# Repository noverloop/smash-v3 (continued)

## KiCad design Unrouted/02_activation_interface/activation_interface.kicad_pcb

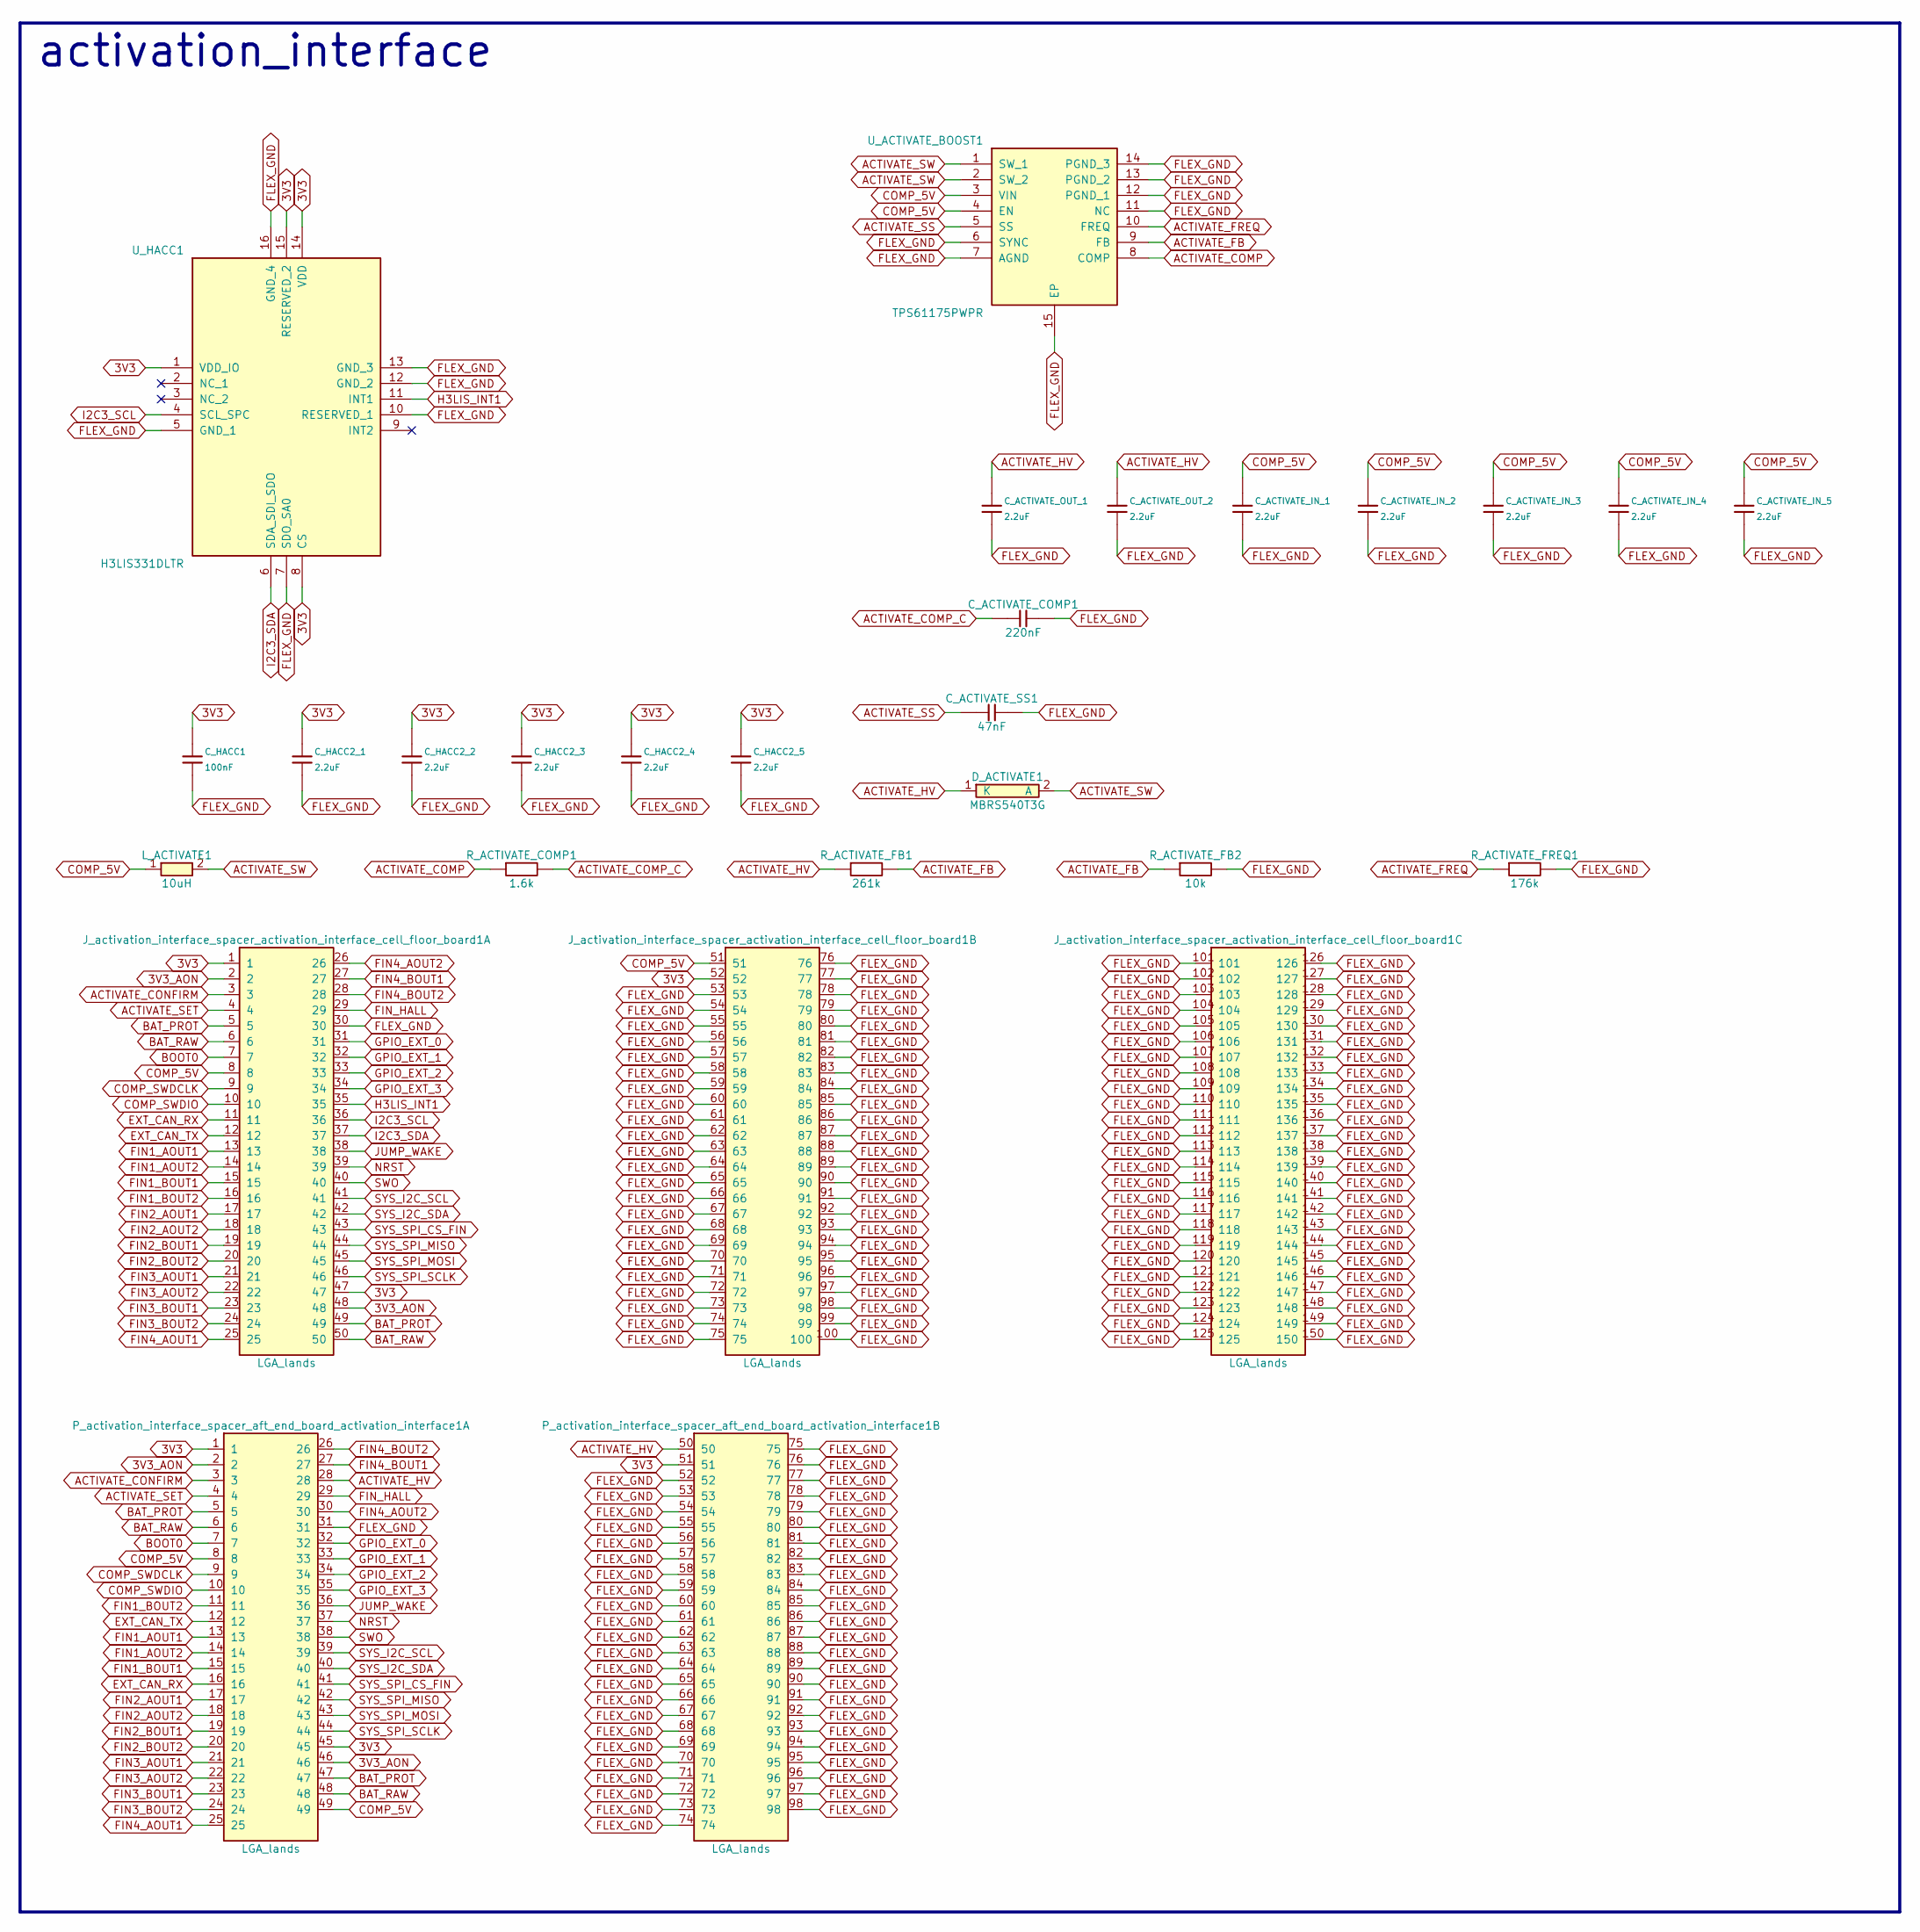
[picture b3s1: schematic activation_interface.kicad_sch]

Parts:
C_ACTIVATE_COMP1: 220nF; Capacitor_SMD_C_0603_1608Metric; MPN C-Series MIL-PRF-32535 X7R 0603 220nF
C_ACTIVATE_IN_1, C_ACTIVATE_IN_2, C_ACTIVATE_IN_3, C_ACTIVATE_IN_4, C_ACTIVATE_IN_5: 2.2uF; Capacitor_SMD_C_0603_1608Metric; MPN C-Series MIL-PRF-32535 X7R 0603 2.2uF
C_ACTIVATE_OUT_1, C_ACTIVATE_OUT_2: 2.2uF; Capacitor_SMD_C_0603_1608Metric; MPN C-Series MIL-PRF-32535 X7R 0603 2.2uF
C_ACTIVATE_SS1: 47nF; Capacitor_SMD_C_0402_1005Metric; MPN C0402 X7R 47nF
C_HACC1: 100nF; Capacitor_SMD_C_0402_1005Metric; MPN C0402 X7R 100nF
C_HACC2_1, C_HACC2_2, C_HACC2_3, C_HACC2_4, C_HACC2_5: 2.2uF; Capacitor_SMD_C_0603_1608Metric; MPN C-Series MIL-PRF-32535 X7R 0603 2.2uF
D_ACTIVATE1: MBRS540T3G; DIOM7958X256N; MPN MBRS540T3G
J_activation_interface_spacer_activation_interface_cell_floor_board1: LGA_lands; J_activation_interface_spacer_activation_interface_cell_flo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; MPN LGA_lands
L_ACTIVATE1: 10uH; INDPM4848X280N; MPN 744043100
P_activation_interface_spacer_aft_end_board_activation_interface1: LGA_lands; P_activation_interface_spacer_aft_end_board_activation_inte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; MPN LGA_lands
R_ACTIVATE_COMP1: 1.6k; Resistor_SMD_R_0402_1005Metric; MPN CRCW0402 1.6k 1% e3
R_ACTIVATE_FB1: 261k; Resistor_SMD_R_0402_1005Metric; MPN CRCW0402 261k 1% e3
R_ACTIVATE_FB2: 10k; Resistor_SMD_R_0402_1005Metric; MPN CRCW0402 10k 1% e3
R_ACTIVATE_FREQ1: 176k; Resistor_SMD_R_0402_1005Metric; MPN CRCW0402 176k 1% e3
U_ACTIVATE_BOOST1: TPS61175PWPR; SOP65P640X120-15N; MPN TPS61175PWPR
U_HACC1: H3LIS331DLTR; LIS3DHTR (LGA-16); MPN H3LIS331DLTR

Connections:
3V3: C_HACC1.1, C_HACC2_1.1, C_HACC2_2.1, C_HACC2_3.1, C_HACC2_4.1, C_HACC2_5.1, J_activation_interface_spacer_activatio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.1, J_activation_interface_spacer_activatio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.47, J_activation_interface_spacer_activatio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.52, P_activation_interface_spacer_aft_end_b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.1, P_activation_interface_spacer_aft_end_b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.45, P_activation_interface_spacer_aft_end_b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.51, U_HACC1.1 (VDD_IO), U_HACC1.8 (CS), U_HACC1.14 (VDD), U_HACC1.15 (RESERVED_2)
3V3_AON: J_activation_interface_spacer_activatio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.2, J_activation_interface_spacer_activatio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.48, P_activation_interface_spacer_aft_end_b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.2, P_activation_interface_spacer_aft_end_b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.46
ACTIVATE_COMP: R_ACTIVATE_COMP1.1, U_ACTIVATE_BOOST1.8 (COMP)
ACTIVATE_COMP_C: C_ACTIVATE_COMP1.1, R_ACTIVATE_COMP1.2
ACTIVATE_CONFIRM: J_activation_interface_spacer_activatio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.3, P_activation_interface_spacer_aft_end_b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.3
ACTIVATE_FB: R_ACTIVATE_FB1.2, R_ACTIVATE_FB2.1, U_ACTIVATE_BOOST1.9 (FB)
ACTIVATE_FREQ: R_ACTIVATE_FREQ1.1, U_ACTIVATE_BOOST1.10 (FREQ)
ACTIVATE_HV: C_ACTIVATE_OUT_1.1, C_ACTIVATE_OUT_2.1, D_ACTIVATE1.1 (K), P_activation_interface_spacer_aft_end_b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.28, P_activation_interface_spacer_aft_end_b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.50, R_ACTIVATE_FB1.1
ACTIVATE_SET: J_activation_interface_spacer_activatio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.4, P_activation_interface_spacer_aft_end_b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.4
ACTIVATE_SS: C_ACTIVATE_SS1.1, U_ACTIVATE_BOOST1.5 (SS)
ACTIVATE_SW: D_ACTIVATE1.2 (A), L_ACTIVATE1.2, U_ACTIVATE_BOOST1.1 (SW_1), U_ACTIVATE_BOOST1.2 (SW_2)
BAT_PROT: J_activation_interface_spacer_activatio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.5, J_activation_interface_spacer_activatio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.49, P_activation_interface_spacer_aft_end_b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.5, P_activation_interface_spacer_aft_end_b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.47
BAT_RAW: J_activation_interface_spacer_activatio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.6, J_activation_interface_spacer_activatio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.50, P_activation_interface_spacer_aft_end_b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.6, P_activation_interface_spacer_aft_end_b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.48
BOOT0: J_activation_interface_spacer_activatio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.7, P_activation_interface_spacer_aft_end_b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.7
COMP_5V: C_ACTIVATE_IN_1.1, C_ACTIVATE_IN_2.1, C_ACTIVATE_IN_3.1, C_ACTIVATE_IN_4.1, C_ACTIVATE_IN_5.1, J_activation_interface_spacer_activatio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.8, J_activation_interface_spacer_activatio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.51, L_ACTIVATE1.1, P_activation_interface_spacer_aft_end_b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.8, P_activation_interface_spacer_aft_end_b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.49, U_ACTIVATE_BOOST1.3 (VIN), U_ACTIVATE_BOOST1.4 (EN)
COMP_SWDCLK: J_activation_interface_spacer_activatio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.9, P_activation_interface_spacer_aft_end_b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.9
COMP_SWDIO: J_activation_interface_spacer_activatio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.10, P_activation_interface_spacer_aft_end_b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.10
EXT_CAN_RX: J_activation_interface_spacer_activatio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.11, P_activation_interface_spacer_aft_end_b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.16
EXT_CAN_TX: J_activation_interface_spacer_activatio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.12, P_activation_interface_spacer_aft_end_b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.12
FIN1_AOUT1: J_activation_interface_spacer_activatio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.13, P_activation_interface_spacer_aft_end_b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.13
FIN1_AOUT2: J_activation_interface_spacer_activatio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.14, P_activation_interface_spacer_aft_end_b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.14
FIN1_BOUT1: J_activation_interface_spacer_activatio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.15, P_activation_interface_spacer_aft_end_b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.15
FIN1_BOUT2: J_activation_interface_spacer_activatio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.16, P_activation_interface_spacer_aft_end_b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.11
FIN2_AOUT1: J_activation_interface_spacer_activatio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.17, P_activation_interface_spacer_aft_end_b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.17
FIN2_AOUT2: J_activation_interface_spacer_activatio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.18, P_activation_interface_spacer_aft_end_b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.18
FIN2_BOUT1: J_activation_interface_spacer_activatio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.19, P_activation_interface_spacer_aft_end_b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.19
FIN2_BOUT2: J_activation_interface_spacer_activatio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.20, P_activation_interface_spacer_aft_end_b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.20
FIN3_AOUT1: J_activation_interface_spacer_activatio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.21, P_activation_interface_spacer_aft_end_b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.21
FIN3_AOUT2: J_activation_interface_spacer_activatio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.22, P_activation_interface_spacer_aft_end_b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.22
FIN3_BOUT1: J_activation_interface_spacer_activatio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.23, P_activation_interface_spacer_aft_end_b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.23
FIN3_BOUT2: J_activation_interface_spacer_activatio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.24, P_activation_interface_spacer_aft_end_b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.24
FIN4_AOUT1: J_activation_interface_spacer_activatio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.25, P_activation_interface_spacer_aft_end_b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.25
FIN4_AOUT2: J_activation_interface_spacer_activatio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.26, P_activation_interface_spacer_aft_end_b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.30
FIN4_BOUT1: J_activation_interface_spacer_activatio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.27, P_activation_interface_spacer_aft_end_b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.27
FIN4_BOUT2: J_activation_interface_spacer_activatio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.28, P_activation_interface_spacer_aft_end_b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.26
FIN_HALL: J_activation_interface_spacer_activatio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.29, P_activation_interface_spacer_aft_end_b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.29
FLEX_GND: C_ACTIVATE_COMP1.2, C_ACTIVATE_IN_1.2, C_ACTIVATE_IN_2.2, C_ACTIVATE_IN_3.2, C_ACTIVATE_IN_4.2, C_ACTIVATE_IN_5.2, C_ACTIVATE_OUT_1.2, C_ACTIVATE_OUT_2.2, C_ACTIVATE_SS1.2, C_HACC1.2, C_HACC2_1.2, C_HACC2_2.2, C_HACC2_3.2, C_HACC2_4.2, C_HACC2_5.2, J_activation_interface_spacer_activatio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.30, J_activation_interface_spacer_activatio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.53, J_activation_interface_spacer_activatio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.54, J_activation_interface_spacer_activatio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.55, J_activation_interface_spacer_activatio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.56, J_activation_interface_spacer_activatio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.57, J_activation_interface_spacer_activatio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.58, J_activation_interface_spacer_activatio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.59, J_activation_interface_spacer_activatio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.60, J_activation_interface_spacer_activatio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.61, J_activation_interface_spacer_activatio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.62, J_activation_interface_spacer_activatio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.63, J_activation_interface_spacer_activatio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.64, J_activation_interface_spacer_activatio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.65, J_activation_interface_spacer_activatio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.66, J_activation_interface_spacer_activatio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.67, J_activation_interface_spacer_activatio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.68, J_activation_interface_spacer_activatio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.69, J_activation_interface_spacer_activatio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.70, J_activation_interface_spacer_activatio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.71, J_activation_interface_spacer_activatio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.72, J_activation_interface_spacer_activatio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.73, J_activation_interface_spacer_activatio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.74, J_activation_interface_spacer_activatio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.75, J_activation_interface_spacer_activatio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.76, J_activation_interface_spacer_activatio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.77, J_activation_interface_spacer_activatio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.78, J_activation_interface_spacer_activatio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.79, J_activation_interface_spacer_activatio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.80, J_activation_interface_spacer_activatio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.81, J_activation_interface_spacer_activatio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.82, J_activation_interface_spacer_activatio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.83, J_activation_interface_spacer_activatio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.84, J_activation_interface_spacer_activatio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.85, J_activation_interface_spacer_activatio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.86, J_activation_interface_spacer_activatio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.87, J_activation_interface_spacer_activatio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.88, J_activation_interface_spacer_activatio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.89, J_activation_interface_spacer_activatio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.90, J_activation_interface_spacer_activatio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.91, J_activation_interface_spacer_activatio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.92, J_activation_interface_spacer_activatio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.93, J_activation_interface_spacer_activatio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.94, J_activation_interface_spacer_activatio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.95, J_activation_interface_spacer_activatio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.96, J_activation_interface_spacer_activatio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.97, J_activation_interface_spacer_activatio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.98, J_activation_interface_spacer_activatio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.99, J_activation_interface_spacer_activatio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.100, J_activation_interface_spacer_activatio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.101, J_activation_interface_spacer_activatio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.102, J_activation_interface_spacer_activatio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.103, J_activation_interface_spacer_activatio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.104, J_activation_interface_spacer_activatio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.105, J_activation_interface_spacer_activatio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.106, J_activation_interface_spacer_activatio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.107, J_activation_interface_spacer_activatio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.108, J_activation_interface_spacer_activatio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.109, J_activation_interface_spacer_activatio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.110, J_activation_interface_spacer_activatio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.111, J_activation_interface_spacer_activatio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.112, J_activation_interface_spacer_activatio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.113, J_activation_interface_spacer_activatio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.114, J_activation_interface_spacer_activatio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.115, J_activation_interface_spacer_activatio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.116, J_activation_interface_spacer_activatio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.117, J_activation_interface_spacer_activatio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.118, J_activation_interface_spacer_activatio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.119, J_activation_interface_spacer_activatio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.120, J_activation_interface_spacer_activatio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.121, J_activation_interface_spacer_activatio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.122, J_activation_interface_spacer_activatio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.123, J_activation_interface_spacer_activatio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.124, J_activation_interface_spacer_activatio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.125, J_activation_interface_spacer_activatio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.126, J_activation_interface_spacer_activatio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.127, J_activation_interface_spacer_activatio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.128, J_activation_interface_spacer_activatio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.129, J_activation_interface_spacer_activatio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.130, J_activation_interface_spacer_activatio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.131, J_activation_interface_spacer_activatio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.132, J_activation_interface_spacer_activatio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.133, J_activation_interface_spacer_activatio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.134, J_activation_interface_spacer_activatio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.135, J_activation_interface_spacer_activatio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.136, J_activation_interface_spacer_activatio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.137, J_activation_interface_spacer_activatio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.138, J_activation_interface_spacer_activatio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.139, J_activation_interface_spacer_activatio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.140, J_activation_interface_spacer_activatio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.141, J_activation_interface_spacer_activatio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.142, J_activation_interface_spacer_activatio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.143, J_activation_interface_spacer_activatio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.144, J_activation_interface_spacer_activatio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.145, J_activation_interface_spacer_activatio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.146, J_activation_interface_spacer_activatio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.147, J_activation_interface_spacer_activatio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.148, J_activation_interface_spacer_activatio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.149, J_activation_interface_spacer_activatio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.150, P_activation_interface_spacer_aft_end_b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.31, P_activation_interface_spacer_aft_end_b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.52, P_activation_interface_spacer_aft_end_b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.53, P_activation_interface_spacer_aft_end_b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.54, P_activation_interface_spacer_aft_end_b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.55, P_activation_interface_spacer_aft_end_b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.56, P_activation_interface_spacer_aft_end_b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.57, P_activation_interface_spacer_aft_end_b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.58, P_activation_interface_spacer_aft_end_b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.59, P_activation_interface_spacer_aft_end_b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.60, P_activation_interface_spacer_aft_end_b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.61, P_activation_interface_spacer_aft_end_b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.62, P_activation_interface_spacer_aft_end_b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.63, P_activation_interface_spacer_aft_end_b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.64, P_activation_interface_spacer_aft_end_b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.65, P_activation_interface_spacer_aft_end_b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.66, P_activation_interface_spacer_aft_end_b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.67, P_activation_interface_spacer_aft_end_b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.68, P_activation_interface_spacer_aft_end_b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.69, P_activation_interface_spacer_aft_end_b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.70, P_activation_interface_spacer_aft_end_b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.71, P_activation_interface_spacer_aft_end_b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.72, P_activation_interface_spacer_aft_end_b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.73, P_activation_interface_spacer_aft_end_b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.74, P_activation_interface_spacer_aft_end_b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.75, P_activation_interface_spacer_aft_end_b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.76, P_activation_interface_spacer_aft_end_b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.77, P_activation_interface_spacer_aft_end_b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.78, P_activation_interface_spacer_aft_end_b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.79, P_activation_interface_spacer_aft_end_b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.80, P_activation_interface_spacer_aft_end_b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.81, P_activation_interface_spacer_aft_end_b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.82, P_activation_interface_spacer_aft_end_b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.83, P_activation_interface_spacer_aft_end_b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.84, P_activation_interface_spacer_aft_end_b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.85, P_activation_interface_spacer_aft_end_b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.86, P_activation_interface_spacer_aft_end_b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.87, P_activation_interface_spacer_aft_end_b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.88, P_activation_interface_spacer_aft_end_b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.89, P_activation_interface_spacer_aft_end_b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.90, P_activation_interface_spacer_aft_end_b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.91, P_activation_interface_spacer_aft_end_b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.92, P_activation_interface_spacer_aft_end_b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.93, P_activation_interface_spacer_aft_end_b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.94, P_activation_interface_spacer_aft_end_b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.95, P_activation_interface_spacer_aft_end_b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.96, P_activation_interface_spacer_aft_end_b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.97, P_activation_interface_spacer_aft_end_b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.98, R_ACTIVATE_FB2.2, R_ACTIVATE_FREQ1.2, U_ACTIVATE_BOOST1.6 (SYNC), U_ACTIVATE_BOOST1.7 (AGND), U_ACTIVATE_BOOST1.11 (NC), U_ACTIVATE_BOOST1.12 (PGND_1), U_ACTIVATE_BOOST1.13 (PGND_2), U_ACTIVATE_BOOST1.14 (PGND_3), U_ACTIVATE_BOOST1.15 (EP), U_HACC1.5 (GND_1), U_HACC1.7 (SDO_SA0), U_HACC1.10 (RESERVED_1), U_HACC1.12 (GND_2), U_HACC1.13 (GND_3), U_HACC1.16 (GND_4)
GPIO_EXT_0: J_activation_interface_spacer_activatio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.31, P_activation_interface_spacer_aft_end_b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.32
GPIO_EXT_1: J_activation_interface_spacer_activatio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.32, P_activation_interface_spacer_aft_end_b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.33
GPIO_EXT_2: J_activation_interface_spacer_activatio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.33, P_activation_interface_spacer_aft_end_b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.34
GPIO_EXT_3: J_activation_interface_spacer_activatio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.34, P_activation_interface_spacer_aft_end_b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.35
H3LIS_INT1: J_activation_interface_spacer_activatio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.35, U_HACC1.11 (INT1)
I2C3_SCL: J_activation_interface_spacer_activatio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.36, U_HACC1.4 (SCL_SPC)
I2C3_SDA: J_activation_interface_spacer_activatio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.37, U_HACC1.6 (SDA_SDI_SDO)
JUMP_WAKE: J_activation_interface_spacer_activatio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.38, P_activation_interface_spacer_aft_end_b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.36
NRST: J_activation_interface_spacer_activatio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.39, P_activation_interface_spacer_aft_end_b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.37
SWO: J_activation_interface_spacer_activatio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.40, P_activation_interface_spacer_aft_end_b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.38
SYS_I2C_SCL: J_activation_interface_spacer_activatio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.41, P_activation_interface_spacer_aft_end_b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.39
SYS_I2C_SDA: J_activation_interface_spacer_activatio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.42, P_activation_interface_spacer_aft_end_b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.40
SYS_SPI_CS_FIN: J_activation_interface_spacer_activatio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.43, P_activation_interface_spacer_aft_end_b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.41
SYS_SPI_MISO: J_activation_interface_spacer_activatio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.44, P_activation_interface_spacer_aft_end_b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.42
SYS_SPI_MOSI: J_activation_interface_spacer_activatio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.45, P_activation_interface_spacer_aft_end_b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.43
SYS_SPI_SCLK: J_activation_interface_spacer_activatio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.46, P_activation_interface_spacer_aft_end_b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.44

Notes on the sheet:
activation_interface

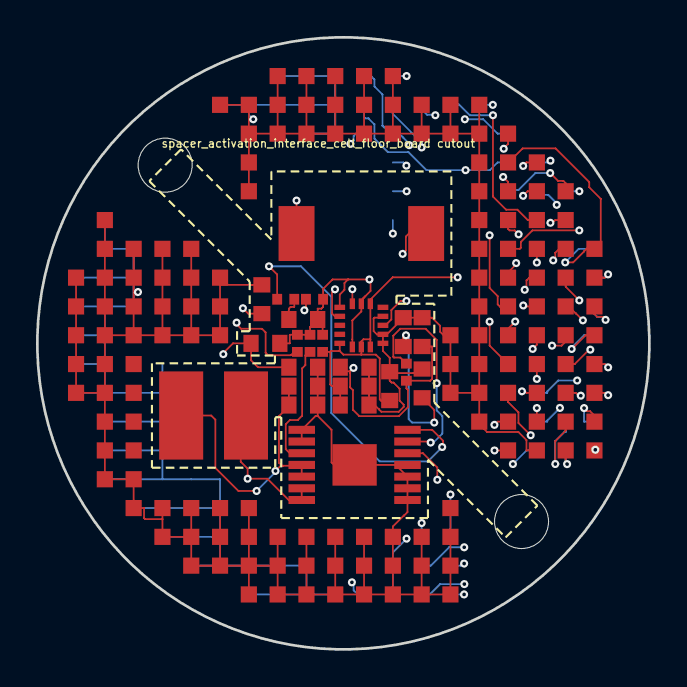
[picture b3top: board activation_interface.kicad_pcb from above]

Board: 14 copper layers, 34.0 x 34.0 mm, 27 parts (1 on the bottom side), 53 nets.

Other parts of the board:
MH1, MH2: smash_mech_potting

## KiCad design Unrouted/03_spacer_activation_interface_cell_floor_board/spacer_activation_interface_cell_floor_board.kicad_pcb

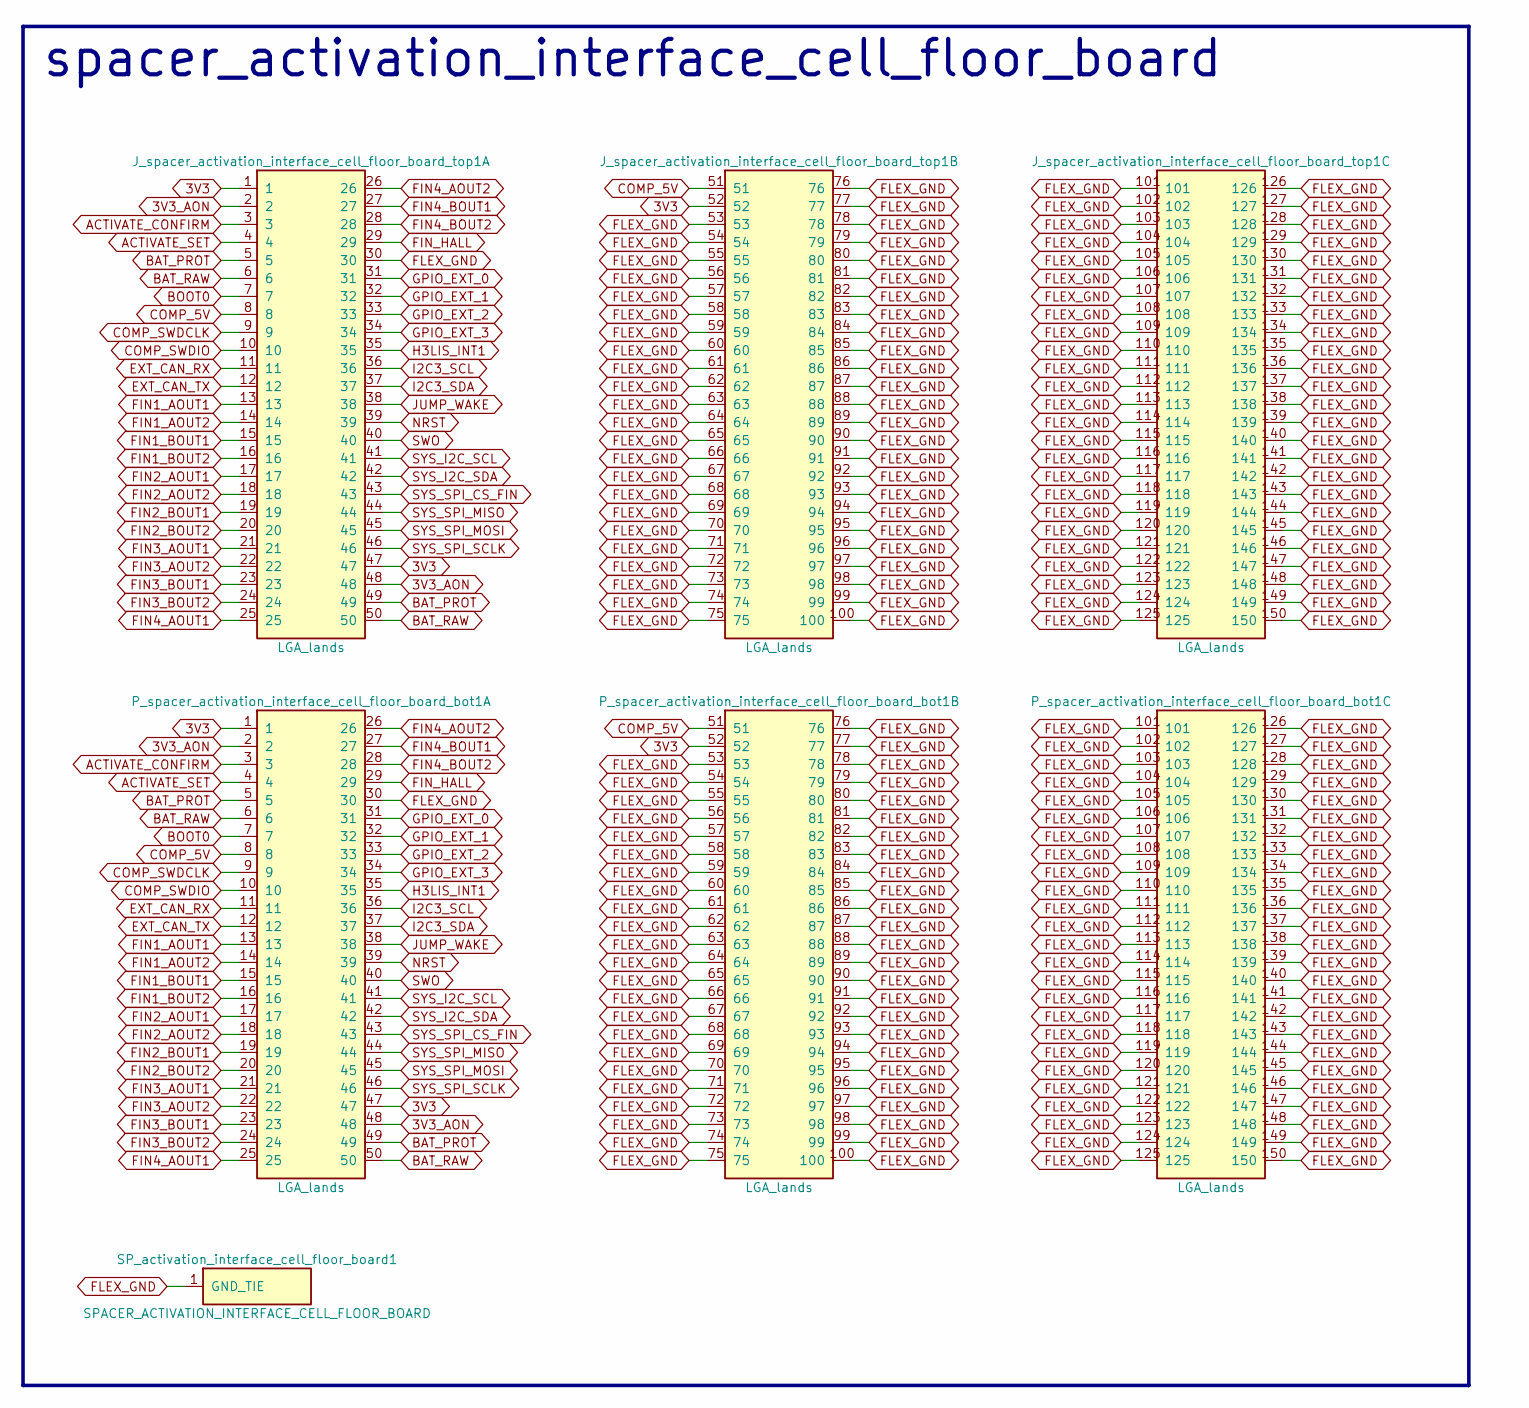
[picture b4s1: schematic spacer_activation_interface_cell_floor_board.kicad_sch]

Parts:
J_spacer_activation_interface_cell_floor_board_top1: LGA_lands; J_spacer_activation_interface_cell_floor_board_top; MPN LGA_lands
P_spacer_activation_interface_cell_floor_board_bot1: LGA_lands; P_spacer_activation_interface_cell_floor_board_bot; MPN LGA_lands
SP_activation_interface_cell_floor_board1: SPACER_ACTIVATION_INTERFACE_CELL_FLOOR_BOARD; Spacer_Mechanical_34mm

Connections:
3V3: J_spacer_activation_interface_cell_floo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.1, J_spacer_activation_interface_cell_floo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.47, J_spacer_activation_interface_cell_floo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.52, P_spacer_activation_interface_cell_floo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.1, P_spacer_activation_interface_cell_floo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.47, P_spacer_activation_interface_cell_floo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.52
3V3_AON: J_spacer_activation_interface_cell_floo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.2, J_spacer_activation_interface_cell_floo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.48, P_spacer_activation_interface_cell_floo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.2, P_spacer_activation_interface_cell_floo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.48
ACTIVATE_CONFIRM: J_spacer_activation_interface_cell_floo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.3, P_spacer_activation_interface_cell_floo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.3
ACTIVATE_SET: J_spacer_activation_interface_cell_floo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.4, P_spacer_activation_interface_cell_floo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.4
BAT_PROT: J_spacer_activation_interface_cell_floo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.5, J_spacer_activation_interface_cell_floo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.49, P_spacer_activation_interface_cell_floo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.5, P_spacer_activation_interface_cell_floo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.49
BAT_RAW: J_spacer_activation_interface_cell_floo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.6, J_spacer_activation_interface_cell_floo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.50, P_spacer_activation_interface_cell_floo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.6, P_spacer_activation_interface_cell_floo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.50
BOOT0: J_spacer_activation_interface_cell_floo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.7, P_spacer_activation_interface_cell_floo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.7
COMP_5V: J_spacer_activation_interface_cell_floo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.8, J_spacer_activation_interface_cell_floo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.51, P_spacer_activation_interface_cell_floo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.8, P_spacer_activation_interface_cell_floo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.51
COMP_SWDCLK: J_spacer_activation_interface_cell_floo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.9, P_spacer_activation_interface_cell_floo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.9
COMP_SWDIO: J_spacer_activation_interface_cell_floo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.10, P_spacer_activation_interface_cell_floo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.10
EXT_CAN_RX: J_spacer_activation_interface_cell_floo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.11, P_spacer_activation_interface_cell_floo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.11
EXT_CAN_TX: J_spacer_activation_interface_cell_floo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.12, P_spacer_activation_interface_cell_floo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.12
FIN1_AOUT1: J_spacer_activation_interface_cell_floo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.13, P_spacer_activation_interface_cell_floo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.13
FIN1_AOUT2: J_spacer_activation_interface_cell_floo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.14, P_spacer_activation_interface_cell_floo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.14
FIN1_BOUT1: J_spacer_activation_interface_cell_floo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.15, P_spacer_activation_interface_cell_floo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.15
FIN1_BOUT2: J_spacer_activation_interface_cell_floo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.16, P_spacer_activation_interface_cell_floo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.16
FIN2_AOUT1: J_spacer_activation_interface_cell_floo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.17, P_spacer_activation_interface_cell_floo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.17
FIN2_AOUT2: J_spacer_activation_interface_cell_floo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.18, P_spacer_activation_interface_cell_floo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.18
FIN2_BOUT1: J_spacer_activation_interface_cell_floo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.19, P_spacer_activation_interface_cell_floo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.19
FIN2_BOUT2: J_spacer_activation_interface_cell_floo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.20, P_spacer_activation_interface_cell_floo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.20
FIN3_AOUT1: J_spacer_activation_interface_cell_floo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.21, P_spacer_activation_interface_cell_floo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.21
FIN3_AOUT2: J_spacer_activation_interface_cell_floo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.22, P_spacer_activation_interface_cell_floo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.22
FIN3_BOUT1: J_spacer_activation_interface_cell_floo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.23, P_spacer_activation_interface_cell_floo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.23
FIN3_BOUT2: J_spacer_activation_interface_cell_floo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.24, P_spacer_activation_interface_cell_floo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.24
FIN4_AOUT1: J_spacer_activation_interface_cell_floo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.25, P_spacer_activation_interface_cell_floo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.25
FIN4_AOUT2: J_spacer_activation_interface_cell_floo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.26, P_spacer_activation_interface_cell_floo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.26
FIN4_BOUT1: J_spacer_activation_interface_cell_floo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.27, P_spacer_activation_interface_cell_floo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.27
FIN4_BOUT2: J_spacer_activation_interface_cell_floo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.28, P_spacer_activation_interface_cell_floo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.28
FIN_HALL: J_spacer_activation_interface_cell_floo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.29, P_spacer_activation_interface_cell_floo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.29
FLEX_GND: J_spacer_activation_interface_cell_floo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.30, J_spacer_activation_interface_cell_floo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.53, J_spacer_activation_interface_cell_floo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.54, J_spacer_activation_interface_cell_floo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.55, J_spacer_activation_interface_cell_floo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.56, J_spacer_activation_interface_cell_floo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.57, J_spacer_activation_interface_cell_floo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.58, J_spacer_activation_interface_cell_floo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.59, J_spacer_activation_interface_cell_floo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.60, J_spacer_activation_interface_cell_floo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.61, J_spacer_activation_interface_cell_floo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.62, J_spacer_activation_interface_cell_floo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.63, J_spacer_activation_interface_cell_floo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.64, J_spacer_activation_interface_cell_floo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.65, J_spacer_activation_interface_cell_floo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.66, J_spacer_activation_interface_cell_floo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.67, J_spacer_activation_interface_cell_floo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.68, J_spacer_activation_interface_cell_floo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.69, J_spacer_activation_interface_cell_floo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.70, J_spacer_activation_interface_cell_floo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.71, J_spacer_activation_interface_cell_floo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.72, J_spacer_activation_interface_cell_floo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.73, J_spacer_activation_interface_cell_floo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.74, J_spacer_activation_interface_cell_floo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.75, J_spacer_activation_interface_cell_floo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.76, J_spacer_activation_interface_cell_floo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.77, J_spacer_activation_interface_cell_floo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.78, J_spacer_activation_interface_cell_floo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.79, J_spacer_activation_interface_cell_floo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.80, J_spacer_activation_interface_cell_floo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.81, J_spacer_activation_interface_cell_floo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.82, J_spacer_activation_interface_cell_floo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.83, J_spacer_activation_interface_cell_floo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.84, J_spacer_activation_interface_cell_floo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.85, J_spacer_activation_interface_cell_floo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.86, J_spacer_activation_interface_cell_floo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.87, J_spacer_activation_interface_cell_floo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.88, J_spacer_activation_interface_cell_floo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.89, J_spacer_activation_interface_cell_floo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.90, J_spacer_activation_interface_cell_floo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.91, J_spacer_activation_interface_cell_floo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.92, J_spacer_activation_interface_cell_floo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.93, J_spacer_activation_interface_cell_floo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.94, J_spacer_activation_interface_cell_floo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.95, J_spacer_activation_interface_cell_floo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.96, J_spacer_activation_interface_cell_floo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.97, J_spacer_activation_interface_cell_floo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.98, J_spacer_activation_interface_cell_floo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.99, J_spacer_activation_interface_cell_floo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.100, J_spacer_activation_interface_cell_floo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.101, J_spacer_activation_interface_cell_floo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.102, J_spacer_activation_interface_cell_floo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.103, J_spacer_activation_interface_cell_floo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.104, J_spacer_activation_interface_cell_floo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.105, J_spacer_activation_interface_cell_floo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.106, J_spacer_activation_interface_cell_floo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.107, J_spacer_activation_interface_cell_floo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.108, J_spacer_activation_interface_cell_floo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.109, J_spacer_activation_interface_cell_floo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.110, J_spacer_activation_interface_cell_floo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.111, J_spacer_activation_interface_cell_floo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.112, J_spacer_activation_interface_cell_floo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.113, J_spacer_activation_interface_cell_floo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.114, J_spacer_activation_interface_cell_floo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.115, J_spacer_activation_interface_cell_floo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.116, J_spacer_activation_interface_cell_floo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.117, J_spacer_activation_interface_cell_floo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.118, J_spacer_activation_interface_cell_floo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.119, J_spacer_activation_interface_cell_floo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.120, J_spacer_activation_interface_cell_floo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.121, J_spacer_activation_interface_cell_floo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.122, J_spacer_activation_interface_cell_floo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.123, J_spacer_activation_interface_cell_floo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.124, J_spacer_activation_interface_cell_floo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.125, J_spacer_activation_interface_cell_floo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.126, J_spacer_activation_interface_cell_floo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.127, J_spacer_activation_interface_cell_floo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.128, J_spacer_activation_interface_cell_floo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.129, J_spacer_activation_interface_cell_floo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.130, J_spacer_activation_interface_cell_floo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.131, J_spacer_activation_interface_cell_floo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.132, J_spacer_activation_interface_cell_floo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.133, J_spacer_activation_interface_cell_floo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.134, J_spacer_activation_interface_cell_floo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.135, J_spacer_activation_interface_cell_floo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.136, J_spacer_activation_interface_cell_floo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.137, J_spacer_activation_interface_cell_floo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.138, J_spacer_activation_interface_cell_floo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.139, J_spacer_activation_interface_cell_floo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.140, J_spacer_activation_interface_cell_floo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.141, J_spacer_activation_interface_cell_floo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.142, J_spacer_activation_interface_cell_floo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.143, J_spacer_activation_interface_cell_floo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.144, J_spacer_activation_interface_cell_floo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.145, J_spacer_activation_interface_cell_floo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.146, J_spacer_activation_interface_cell_floo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.147, J_spacer_activation_interface_cell_floo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.148, J_spacer_activation_interface_cell_floo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.149, J_spacer_activation_interface_cell_floo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.150, P_spacer_activation_interface_cell_floo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.30, P_spacer_activation_interface_cell_floo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.53, P_spacer_activation_interface_cell_floo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.54, P_spacer_activation_interface_cell_floo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.55, P_spacer_activation_interface_cell_floo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.56, P_spacer_activation_interface_cell_floo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.57, P_spacer_activation_interface_cell_floo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.58, P_spacer_activation_interface_cell_floo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.59, P_spacer_activation_interface_cell_floo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.60, P_spacer_activation_interface_cell_floo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.61, P_spacer_activation_interface_cell_floo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.62, P_spacer_activation_interface_cell_floo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.63, P_spacer_activation_interface_cell_floo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.64, P_spacer_activation_interface_cell_floo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.65, P_spacer_activation_interface_cell_floo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.66, P_spacer_activation_interface_cell_floo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.67, P_spacer_activation_interface_cell_floo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.68, P_spacer_activation_interface_cell_floo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.69, P_spacer_activation_interface_cell_floo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.70, P_spacer_activation_interface_cell_floo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.71, P_spacer_activation_interface_cell_floo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.72, P_spacer_activation_interface_cell_floo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.73, P_spacer_activation_interface_cell_floo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.74, P_spacer_activation_interface_cell_floo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.75, P_spacer_activation_interface_cell_floo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.76, P_spacer_activation_interface_cell_floo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.77, P_spacer_activation_interface_cell_floo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.78, P_spacer_activation_interface_cell_floo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.79, P_spacer_activation_interface_cell_floo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.80, P_spacer_activation_interface_cell_floo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.81, P_spacer_activation_interface_cell_floo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.82, P_spacer_activation_interface_cell_floo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.83, P_spacer_activation_interface_cell_floo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.84, P_spacer_activation_interface_cell_floo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.85, P_spacer_activation_interface_cell_floo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.86, P_spacer_activation_interface_cell_floo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.87, P_spacer_activation_interface_cell_floo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.88, P_spacer_activation_interface_cell_floo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.89, P_spacer_activation_interface_cell_floo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.90, P_spacer_activation_interface_cell_floo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.91, P_spacer_activation_interface_cell_floo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.92, P_spacer_activation_interface_cell_floo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.93, P_spacer_activation_interface_cell_floo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.94, P_spacer_activation_interface_cell_floo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.95, P_spacer_activation_interface_cell_floo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.96, P_spacer_activation_interface_cell_floo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.97, P_spacer_activation_interface_cell_floo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.98, P_spacer_activation_interface_cell_floo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.99, P_spacer_activation_interface_cell_floo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.100, P_spacer_activation_interface_cell_floo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.101, P_spacer_activation_interface_cell_floo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.102, P_spacer_activation_interface_cell_floo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.103, P_spacer_activation_interface_cell_floo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.104, P_spacer_activation_interface_cell_floo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.105, P_spacer_activation_interface_cell_floo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.106, P_spacer_activation_interface_cell_floo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.107, P_spacer_activation_interface_cell_floo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.108, P_spacer_activation_interface_cell_floo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.109, P_spacer_activation_interface_cell_floo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.110, P_spacer_activation_interface_cell_floo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.111, P_spacer_activation_interface_cell_floo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.112, P_spacer_activation_interface_cell_floo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.113, P_spacer_activation_interface_cell_floo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.114, P_spacer_activation_interface_cell_floo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.115, P_spacer_activation_interface_cell_floo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.116, P_spacer_activation_interface_cell_floo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.117, P_spacer_activation_interface_cell_floo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.118, P_spacer_activation_interface_cell_floo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.119, P_spacer_activation_interface_cell_floo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.120, P_spacer_activation_interface_cell_floo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.121, P_spacer_activation_interface_cell_floo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.122, P_spacer_activation_interface_cell_floo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.123, P_spacer_activation_interface_cell_floo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.124, P_spacer_activation_interface_cell_floo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.125, P_spacer_activation_interface_cell_floo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.126, P_spacer_activation_interface_cell_floo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.127, P_spacer_activation_interface_cell_floo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.128, P_spacer_activation_interface_cell_floo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.129, P_spacer_activation_interface_cell_floo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.130, P_spacer_activation_interface_cell_floo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.131, P_spacer_activation_interface_cell_floo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.132, P_spacer_activation_interface_cell_floo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.133, P_spacer_activation_interface_cell_floo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.134, P_spacer_activation_interface_cell_floo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.135, P_spacer_activation_interface_cell_floo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.136, P_spacer_activation_interface_cell_floo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.137, P_spacer_activation_interface_cell_floo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.138, P_spacer_activation_interface_cell_floo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.139, P_spacer_activation_interface_cell_floo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.140, P_spacer_activation_interface_cell_floo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.141, P_spacer_activation_interface_cell_floo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.142, P_spacer_activation_interface_cell_floo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.143, P_spacer_activation_interface_cell_floo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.144, P_spacer_activation_interface_cell_floo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.145, P_spacer_activation_interface_cell_floo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.146, P_spacer_activation_interface_cell_floo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.147, P_spacer_activation_interface_cell_floo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.148, P_spacer_activation_interface_cell_floo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.149, P_spacer_activation_interface_cell_floo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.150, SP_activation_interface_cell_floor_boar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.1
GPIO_EXT_0: J_spacer_activation_interface_cell_floo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.31, P_spacer_activation_interface_cell_floo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.31
GPIO_EXT_1: J_spacer_activation_interface_cell_floo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.32, P_spacer_activation_interface_cell_floo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.32
GPIO_EXT_2: J_spacer_activation_interface_cell_floo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.33, P_spacer_activation_interface_cell_floo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.33
GPIO_EXT_3: J_spacer_activation_interface_cell_floo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.34, P_spacer_activation_interface_cell_floo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.34
H3LIS_INT1: J_spacer_activation_interface_cell_floo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.35, P_spacer_activation_interface_cell_floo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.35
I2C3_SCL: J_spacer_activation_interface_cell_floo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.36, P_spacer_activation_interface_cell_floo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.36
I2C3_SDA: J_spacer_activation_interface_cell_floo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.37, P_spacer_activation_interface_cell_floo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.37
JUMP_WAKE: J_spacer_activation_interface_cell_floo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.38, P_spacer_activation_interface_cell_floo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.38
NRST: J_spacer_activation_interface_cell_floo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.39, P_spacer_activation_interface_cell_floo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.39
SWO: J_spacer_activation_interface_cell_floo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.40, P_spacer_activation_interface_cell_floo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.40
SYS_I2C_SCL: J_spacer_activation_interface_cell_floo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.41, P_spacer_activation_interface_cell_floo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.41
SYS_I2C_SDA: J_spacer_activation_interface_cell_floo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.42, P_spacer_activation_interface_cell_floo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.42
SYS_SPI_CS_FIN: J_spacer_activation_interface_cell_floo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.43, P_spacer_activation_interface_cell_floo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.43
SYS_SPI_MISO: J_spacer_activation_interface_cell_floo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.44, P_spacer_activation_interface_cell_floo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.44
SYS_SPI_MOSI: J_spacer_activation_interface_cell_floo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.45, P_spacer_activation_interface_cell_floo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.45
SYS_SPI_SCLK: J_spacer_activation_interface_cell_floo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.46, P_spacer_activation_interface_cell_floo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.46

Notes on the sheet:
spacer_activation_interface_cell_floor_board

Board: 2 copper layers, 5 parts (1 on the bottom side), 46 nets, no tracks yet.

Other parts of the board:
MH1, MH2: smash_mech_potting
